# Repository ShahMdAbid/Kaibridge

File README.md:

<div align="center">
  <h1>Kaibridge</h1>
  <p><b>An open-source framework connecting AI agents to KiCad — enabling headless PCB design: architecting circuits from intent, sourcing verified components, compiling multi-sheet schematics, optimizing placement along with deterministic visual push-shove and routing alongside a human engineer in the loop</p>

</div>

<br/>

### Documentation

* [Core Capabilities](docs/core-capabilities.md)
* [System Architecture ](docs/architecture.md)
* [Contributing Guidelines](docs/contributing.md)
* [Changelog](CHANGELOG.md)
* [Issue Tracker](https://github.com/ShahMdAbid/Kaibridge/issues)

## Prerequisites & Installation

### 1. System Requirements
- **Python**: 3.10 or higher
- **KiCad**: KiCad 10.0 (or 9.0/8.0) with `kicad-cli` and bundled Python interpreter
- **Java**: Java 17+ LTS (required for Freerouting headless autorouting)

### 2. Installation
Clone the repository and install Kaibridge in editable mode:
```bash
git clone https://github.com/ShahMdAbid/Kaibridge.git
cd Kaibridge
pip install -e .
```

### 3. Autorouter Setup (Freerouting)
For headless trace routing (`kaibridge route`):
1. Download `freerouting-2.4.1.jar` from [Freerouting Releases](https://github.com/freerouting/freerouting/releases).
2. Place `freerouting-2.4.1.jar` in the Kaibridge root directory, or specify its location in `kicad_paths.json`.

### 4. Verify Installation & Test Suite
```bash
kaibridge --help
pytest
```

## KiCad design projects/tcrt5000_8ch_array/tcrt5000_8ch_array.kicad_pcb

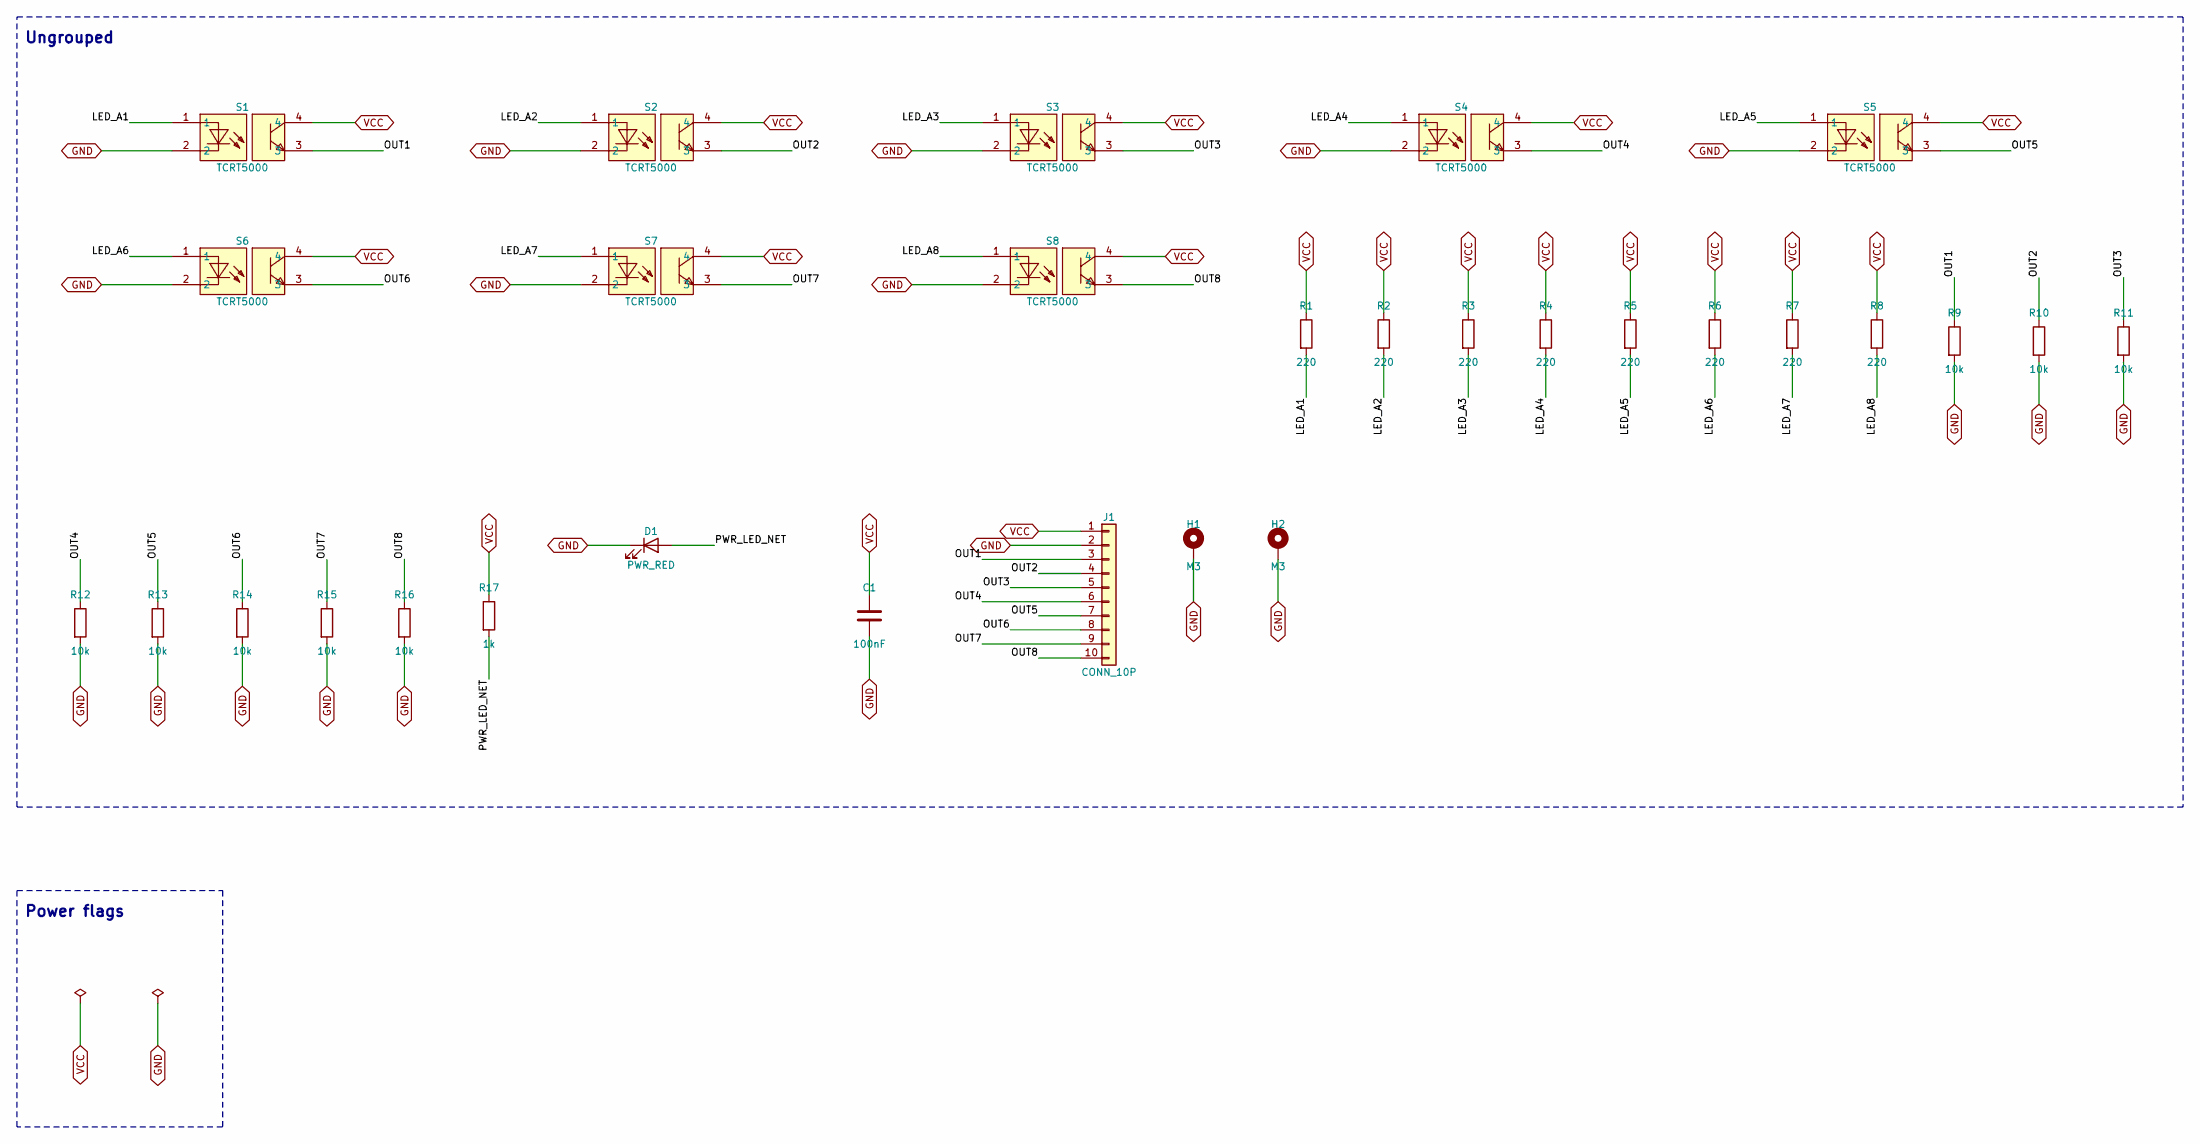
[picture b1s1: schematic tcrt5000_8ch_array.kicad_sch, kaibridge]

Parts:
C1: 100nF; C_Disc_D5.0mm_W2.5mm_P5.00mm; LCSC C66567
D1: PWR_RED; LED_D3.0mm; LCSC C1004
H1, H2: M3; MountingHole_3.2mm_M3_Pad
J1: CONN_10P; PinHeader_1x10_P2.54mm_Vertical; LCSC C2887
R1, R2, R3, R4, R5, R6, R7, R8: 220; R_Axial_DIN0207_L6.3mm_D2.5mm_P7.62mm_Horizontal; LCSC C65241
R9, R10, R11, R12, R13, R14, R15, R16: 10k; R_Axial_DIN0207_L6.3mm_D2.5mm_P7.62mm_Horizontal; LCSC C65240
R17: 1k; R_Axial_DIN0207_L6.3mm_D2.5mm_P7.62mm_Horizontal; LCSC C65242
S1, S2, S3, S4, S5, S6, S7, S8: TCRT5000; OPTO-TH_TCRT5000; LCSC C2984661

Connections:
GND: C1.2, D1.1 (K), H1.1, H2.1, J1.2, R9.2, R10.2, R11.2, R12.2, R13.2, R14.2, R15.2, R16.2, S1.2, S2.2, S3.2, S4.2, S5.2, S6.2, S7.2, S8.2
LED_A1: R1.2, S1.1
LED_A2: R2.2, S2.1
LED_A3: R3.2, S3.1
LED_A4: R4.2, S4.1
LED_A5: R5.2, S5.1
LED_A6: R6.2, S6.1
LED_A7: R7.2, S7.1
LED_A8: R8.2, S8.1
OUT1: J1.3, R9.1, S1.3
OUT2: J1.4, R10.1, S2.3
OUT3: J1.5, R11.1, S3.3
OUT4: J1.6, R12.1, S4.3
OUT5: J1.7, R13.1, S5.3
OUT6: J1.8, R14.1, S6.3
OUT7: J1.9, R15.1, S7.3
OUT8: J1.10, R16.1, S8.3
PWR_LED_NET: D1.2 (A), R17.2
VCC: C1.1, J1.1, R1.1, R2.1, R3.1, R4.1, R5.1, R6.1, R7.1, R8.1, R17.1, S1.4, S2.4, S3.4, S4.4, S5.4, S6.4, S7.4, S8.4

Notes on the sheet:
Ungrouped
Power flags

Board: 2 copper layers, 30 parts (0 on the bottom side), 19 nets, no tracks yet.

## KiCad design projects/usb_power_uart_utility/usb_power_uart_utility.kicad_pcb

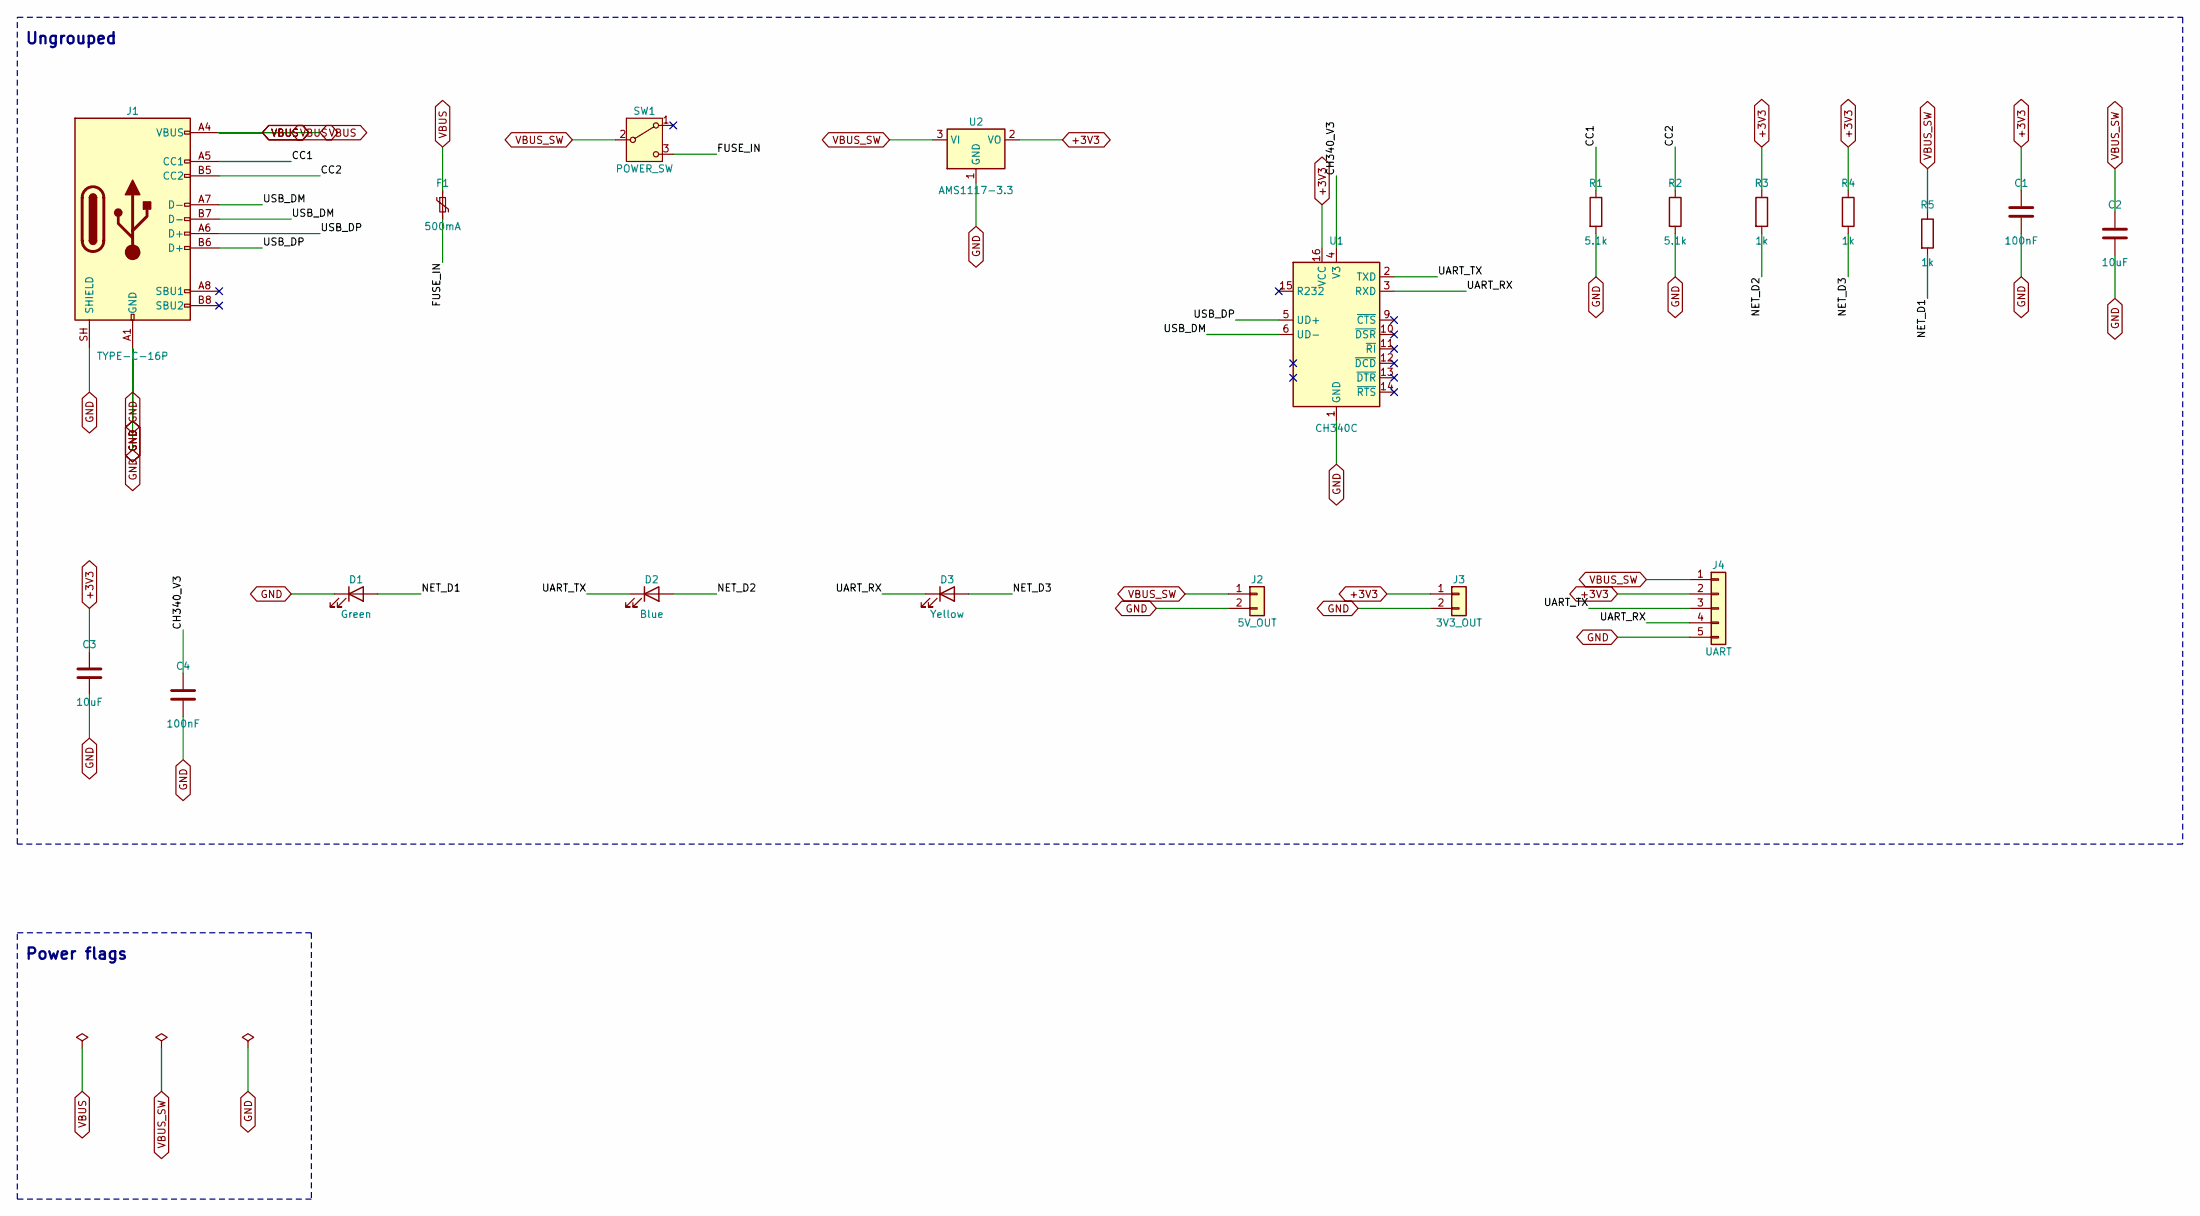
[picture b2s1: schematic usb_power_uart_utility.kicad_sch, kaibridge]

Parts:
C1, C4: 100nF; C_0805_2012Metric; JLCPCB_Class Basic Part
C2, C3: 10uF; C_0805_2012Metric; JLCPCB_Class Basic Part
D1: Green; LED_0805_2012Metric; JLCPCB_Class Basic Part
D2: Blue; LED_0805_2012Metric; JLCPCB_Class Basic Part
D3: Yellow; LED_0805_2012Metric; JLCPCB_Class Basic Part
F1: 500mA; Fuse_1206_3216Metric; JLCPCB_Class Basic Part
J1: TYPE-C-16P; USB_C_Receptacle_HRO_TYPE-C-31-M-12; JLCPCB_Class Basic Part
J2: 5V_OUT; PinHeader_1x02_P2.54mm_Vertical
J3: 3V3_OUT; PinHeader_1x02_P2.54mm_Vertical
J4: UART; PinHeader_1x05_P2.54mm_Vertical
R1, R2: 5.1k; R_0805_2012Metric; JLCPCB_Class Basic Part
R3, R4, R5: 1k; R_0805_2012Metric; JLCPCB_Class Basic Part
SW1: POWER_SW; SW_SPDT_PCM12; JLCPCB_Class Basic Part
U1: CH340C; SOIC-16_3.9x9.9mm_P1.27mm; JLCPCB_Class Basic Part
U2: AMS1117-3.3; SOT-223-3_TabPin2; JLCPCB_Class Basic Part

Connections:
+3V3: C1.1, C3.1, J3.1, J4.2, R3.1, R4.1, U1.16 (VCC), U2.2 (VO)
CC1: J1.A5 (CC1), R1.1
CC2: J1.B5 (CC2), R2.1
CH340_V3: C4.1, U1.4 (V3)
FUSE_IN: F1.2, SW1.3 (C)
GND: C1.2, C2.2, C3.2, C4.2, D1.1 (K), J1.A1 (GND), J1.A12 (GND), J1.B1 (GND), J1.B12 (GND), J1.SH (SHIELD), J2.2, J3.2, J4.5, R1.2, R2.2, U1.1 (GND), U2.1 (GND)
NET_D1: D1.2 (A), R5.2
NET_D2: D2.2 (A), R3.2
NET_D3: D3.2 (A), R4.2
UART_RX: D3.1 (K), J4.4, U1.3 (RXD)
UART_TX: D2.1 (K), J4.3, U1.2 (TXD)
USB_DM: J1.A7 (D-), J1.B7 (D-), U1.6 (UD-)
USB_DP: J1.A6 (D+), J1.B6 (D+), U1.5 (UD+)
VBUS: F1.1, J1.A4 (VBUS), J1.A9 (VBUS), J1.B4 (VBUS), J1.B9 (VBUS)
VBUS_SW: C2.1, J2.1, J4.1, R5.1, SW1.2 (B), U2.3 (VI)

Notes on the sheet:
Ungrouped
Power flags

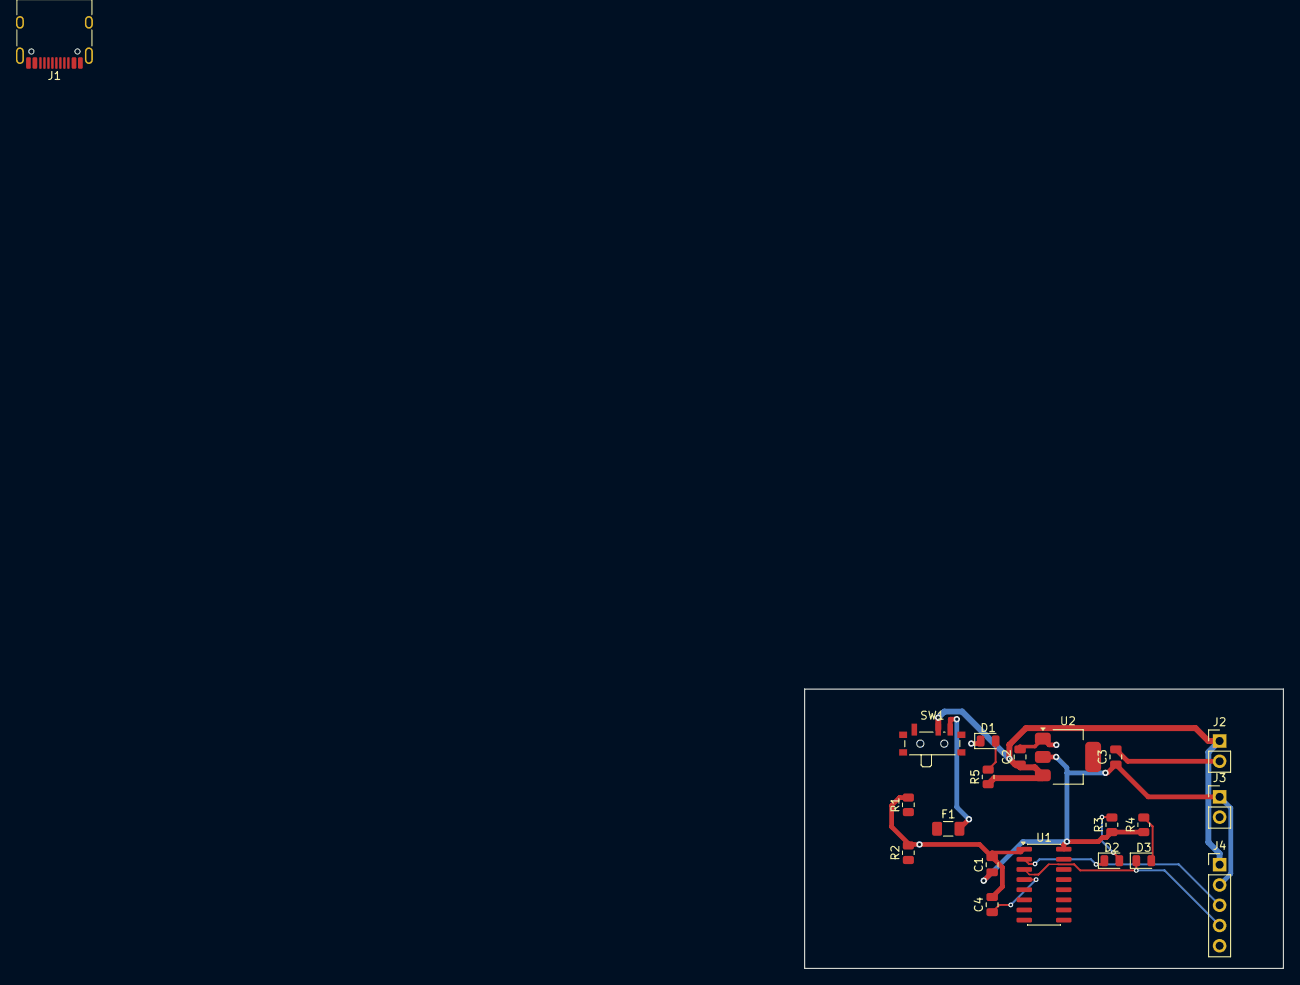
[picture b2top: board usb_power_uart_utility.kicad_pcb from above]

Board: 2 copper layers, 60.0 x 35.0 mm, 20 parts (0 on the bottom side), 15 nets.

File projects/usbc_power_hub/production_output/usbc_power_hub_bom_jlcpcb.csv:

Comment,Designator,Footprint,LCSC Part #
1.2k,R3,R_0805_2012Metric,
10uF,"C1,C2,C3",C_0805_2012Metric,
1k,"R4,R5,R6",R_0805_2012Metric,
5.1k,"R1,R2",R_0805_2012Metric,
AMS1117-3.3,U2,SOT-223-3_L6.5-W3.4-P2.30-LS7.0-BR,
CHRG_RED,D1,LED_0805_2012Metric,
LiPo_BAT,J2,PinHeader_1x02_P2.54mm_Vertical,
PWR_3V3_BLU,D3,LED_0805_2012Metric,
Power_Out,J3,PinHeader_1x04_P2.54mm_Vertical,
STDBY_GRN,D2,LED_0805_2012Metric,
TP4056,U1,ESOP-8_L4.9-W3.9-P1.27-LS6.0-BL-EP,
USB_C_16P,J1,USB_C_Receptacle_HRO_TYPE-C-31-M-12,

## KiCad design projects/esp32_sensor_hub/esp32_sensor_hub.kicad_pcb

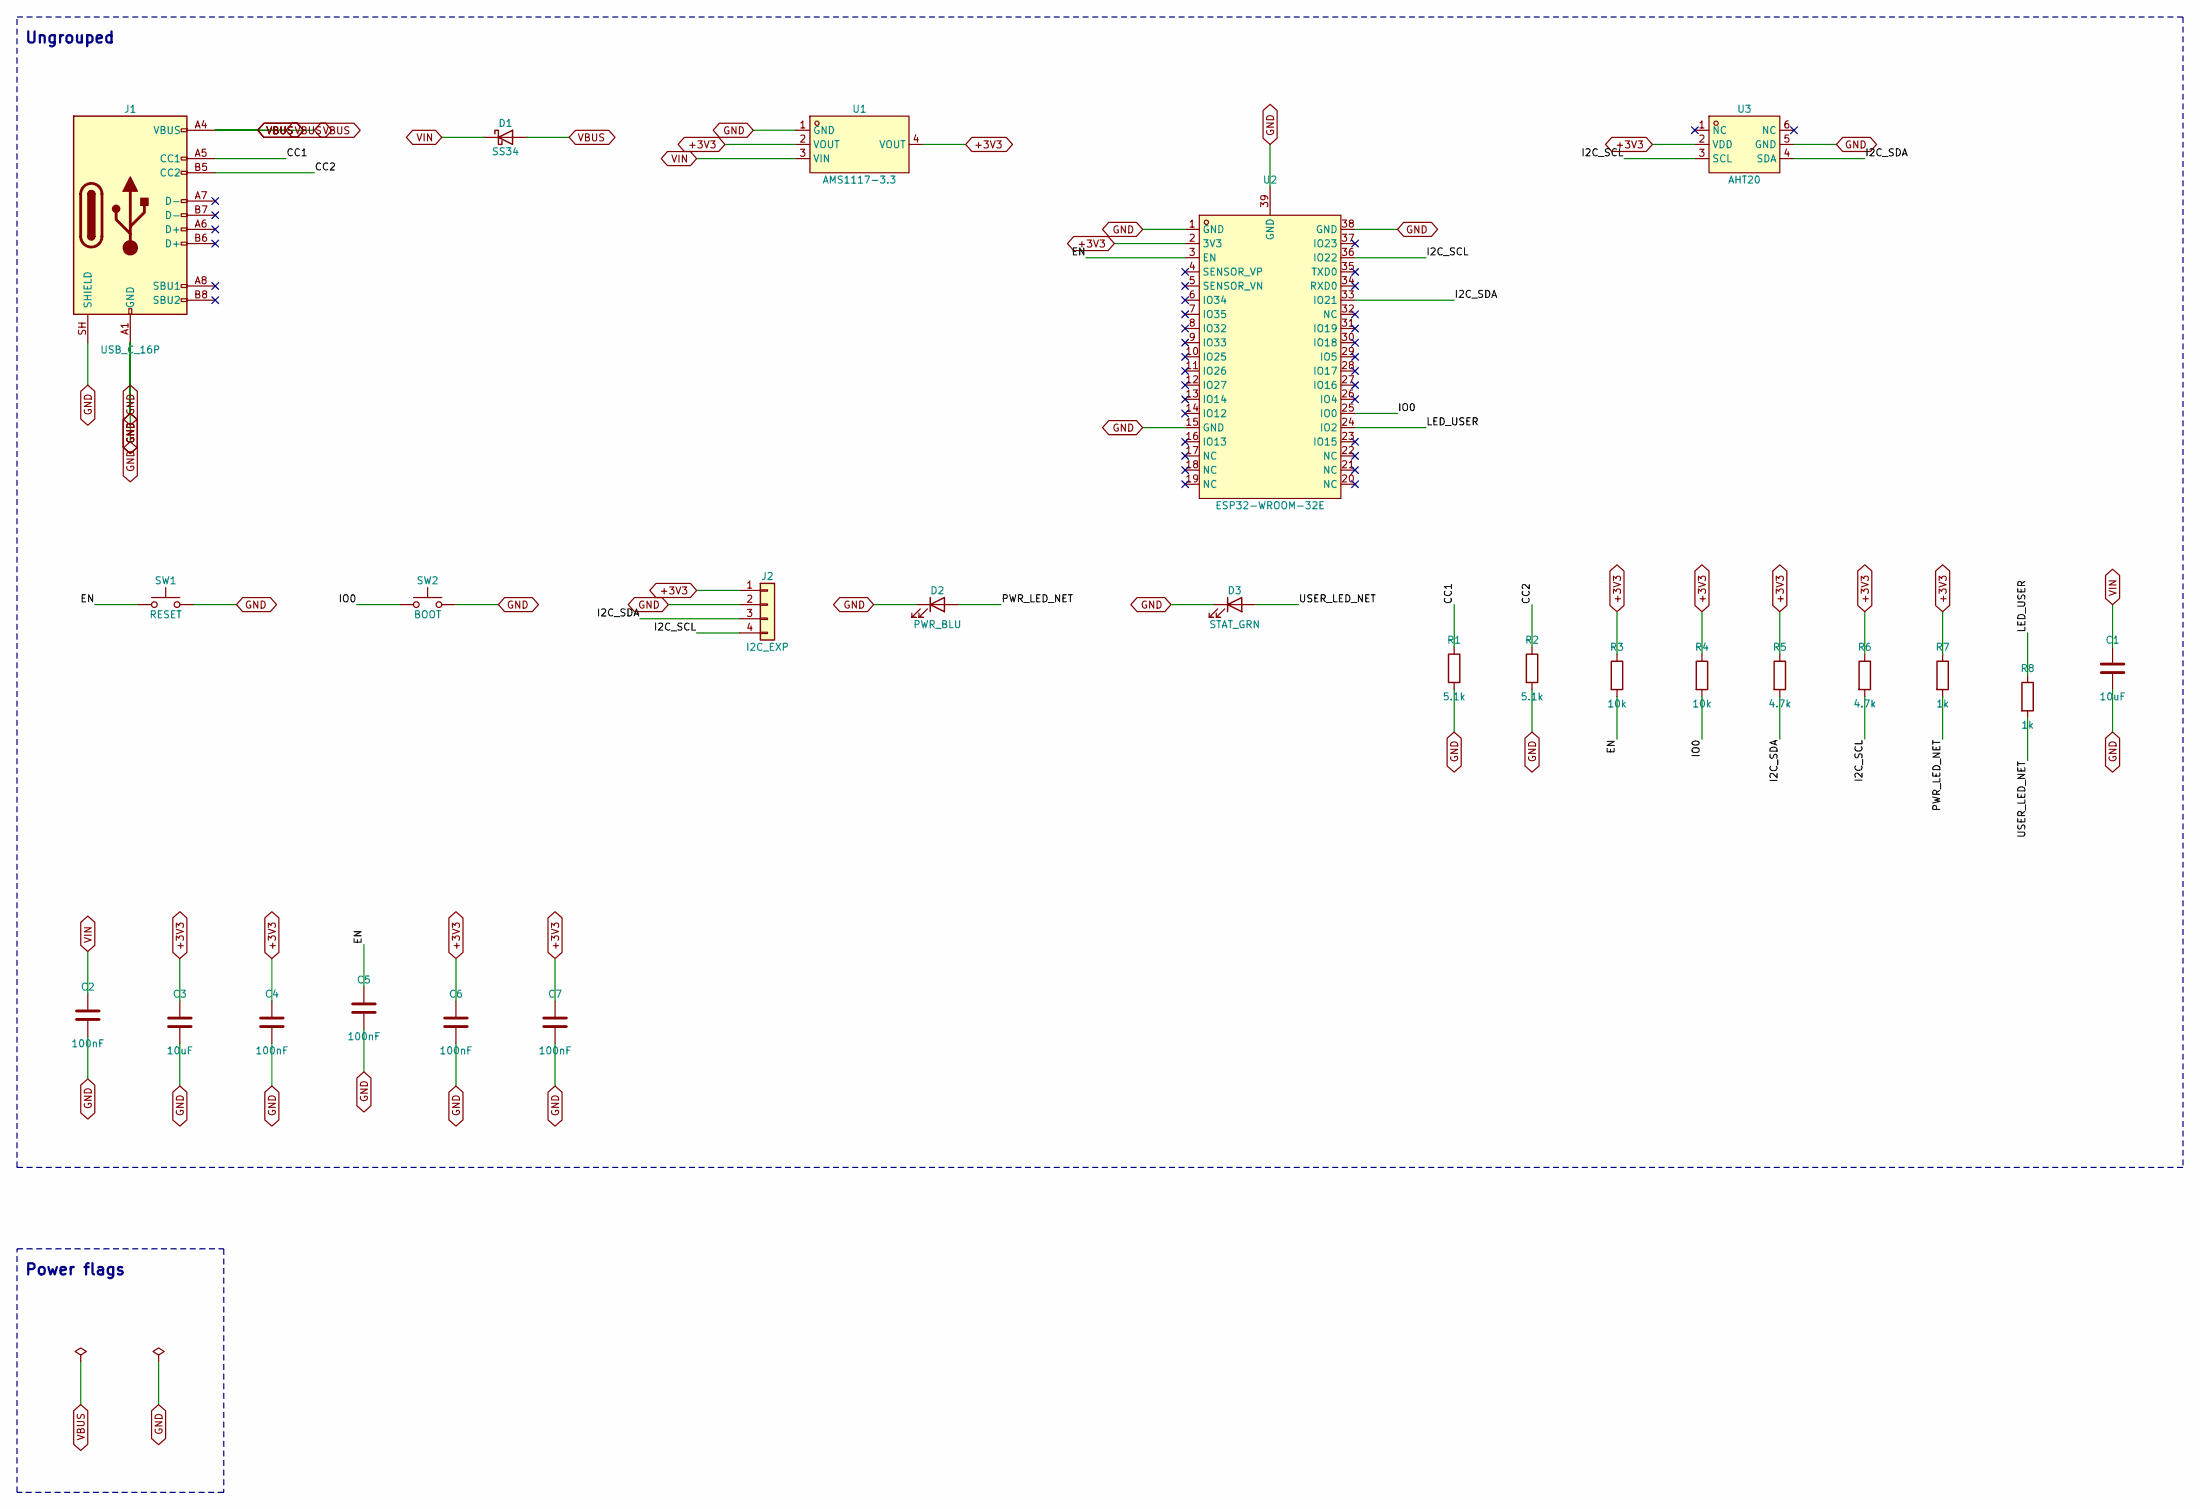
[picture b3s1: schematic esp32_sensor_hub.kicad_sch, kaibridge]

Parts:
C1, C3: 10uF; C_0805_2012Metric; LCSC C15850
C2, C4, C5, C6, C7: 100nF; C_0805_2012Metric; LCSC C28233
D1: SS34; D_SMA; LCSC C8678
D2: PWR_BLU; LED_0805_2012Metric; LCSC C84258
D3: STAT_GRN; LED_0805_2012Metric; LCSC C84257
J1: USB_C_16P; USB_C_Receptacle_HRO_TYPE-C-31-M-12; LCSC C165948
J2: I2C_EXP; PinHeader_1x04_P2.54mm_Vertical; LCSC C2883
R1, R2: 5.1k; R_0805_2012Metric; LCSC C23186
R3, R4: 10k; R_0805_2012Metric; LCSC C17414
R5, R6: 4.7k; R_0805_2012Metric; LCSC C23162
R7, R8: 1k; R_0805_2012Metric; LCSC C17513
SW1: RESET; SW_SPST_PTS645Sx43SMTR92; LCSC C318884
SW2: BOOT; SW_SPST_PTS645Sx43SMTR92; LCSC C318884
U1: AMS1117-3.3; SOT-223-3_L6.5-W3.4-P2.30-LS7.0-BR; LCSC C6186
U2: ESP32-WROOM-32E; WIFI-SMD_ESP32-WROOM-32E; LCSC C701341
U3: AHT20; SENSOR-SMD-6_AHT20; LCSC C3012622

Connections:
+3V3: C3.1, C4.1, C6.1, C7.1, J2.1, R3.1, R4.1, R5.1, R6.1, R7.1, U1.2 (VOUT), U1.4 (VOUT), U2.2 (3V3), U3.2 (VDD)
CC1: J1.A5 (CC1), R1.1
CC2: J1.B5 (CC2), R2.1
EN: C5.1, R3.2, SW1.1, U2.3 (EN)
GND: C1.2, C2.2, C3.2, C4.2, C5.2, C6.2, C7.2, D2.1 (K), D3.1 (K), J1.A1 (GND), J1.A12 (GND), J1.B1 (GND), J1.B12 (GND), J1.SH (SHIELD), J2.2, R1.2, R2.2, SW1.2, SW2.2, U1.1 (GND), U2.1 (GND), U2.15 (GND), U2.38 (GND), U2.39 (GND), U3.5 (GND)
I2C_SCL: J2.4, R6.2, U2.36 (IO22), U3.3 (SCL)
I2C_SDA: J2.3, R5.2, U2.33 (IO21), U3.4 (SDA)
IO0: R4.2, SW2.1, U2.25 (IO0)
LED_USER: R8.1, U2.24 (IO2)
PWR_LED_NET: D2.2 (A), R7.2
USER_LED_NET: D3.2 (A), R8.2
VBUS: D1.2 (A), J1.A4 (VBUS), J1.A9 (VBUS), J1.B4 (VBUS), J1.B9 (VBUS)
VIN: C1.1, C2.1, D1.1 (K), U1.3 (VIN)

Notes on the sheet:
Ungrouped
Power flags

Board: 2 copper layers, 25 parts (0 on the bottom side), 13 nets, no tracks yet.

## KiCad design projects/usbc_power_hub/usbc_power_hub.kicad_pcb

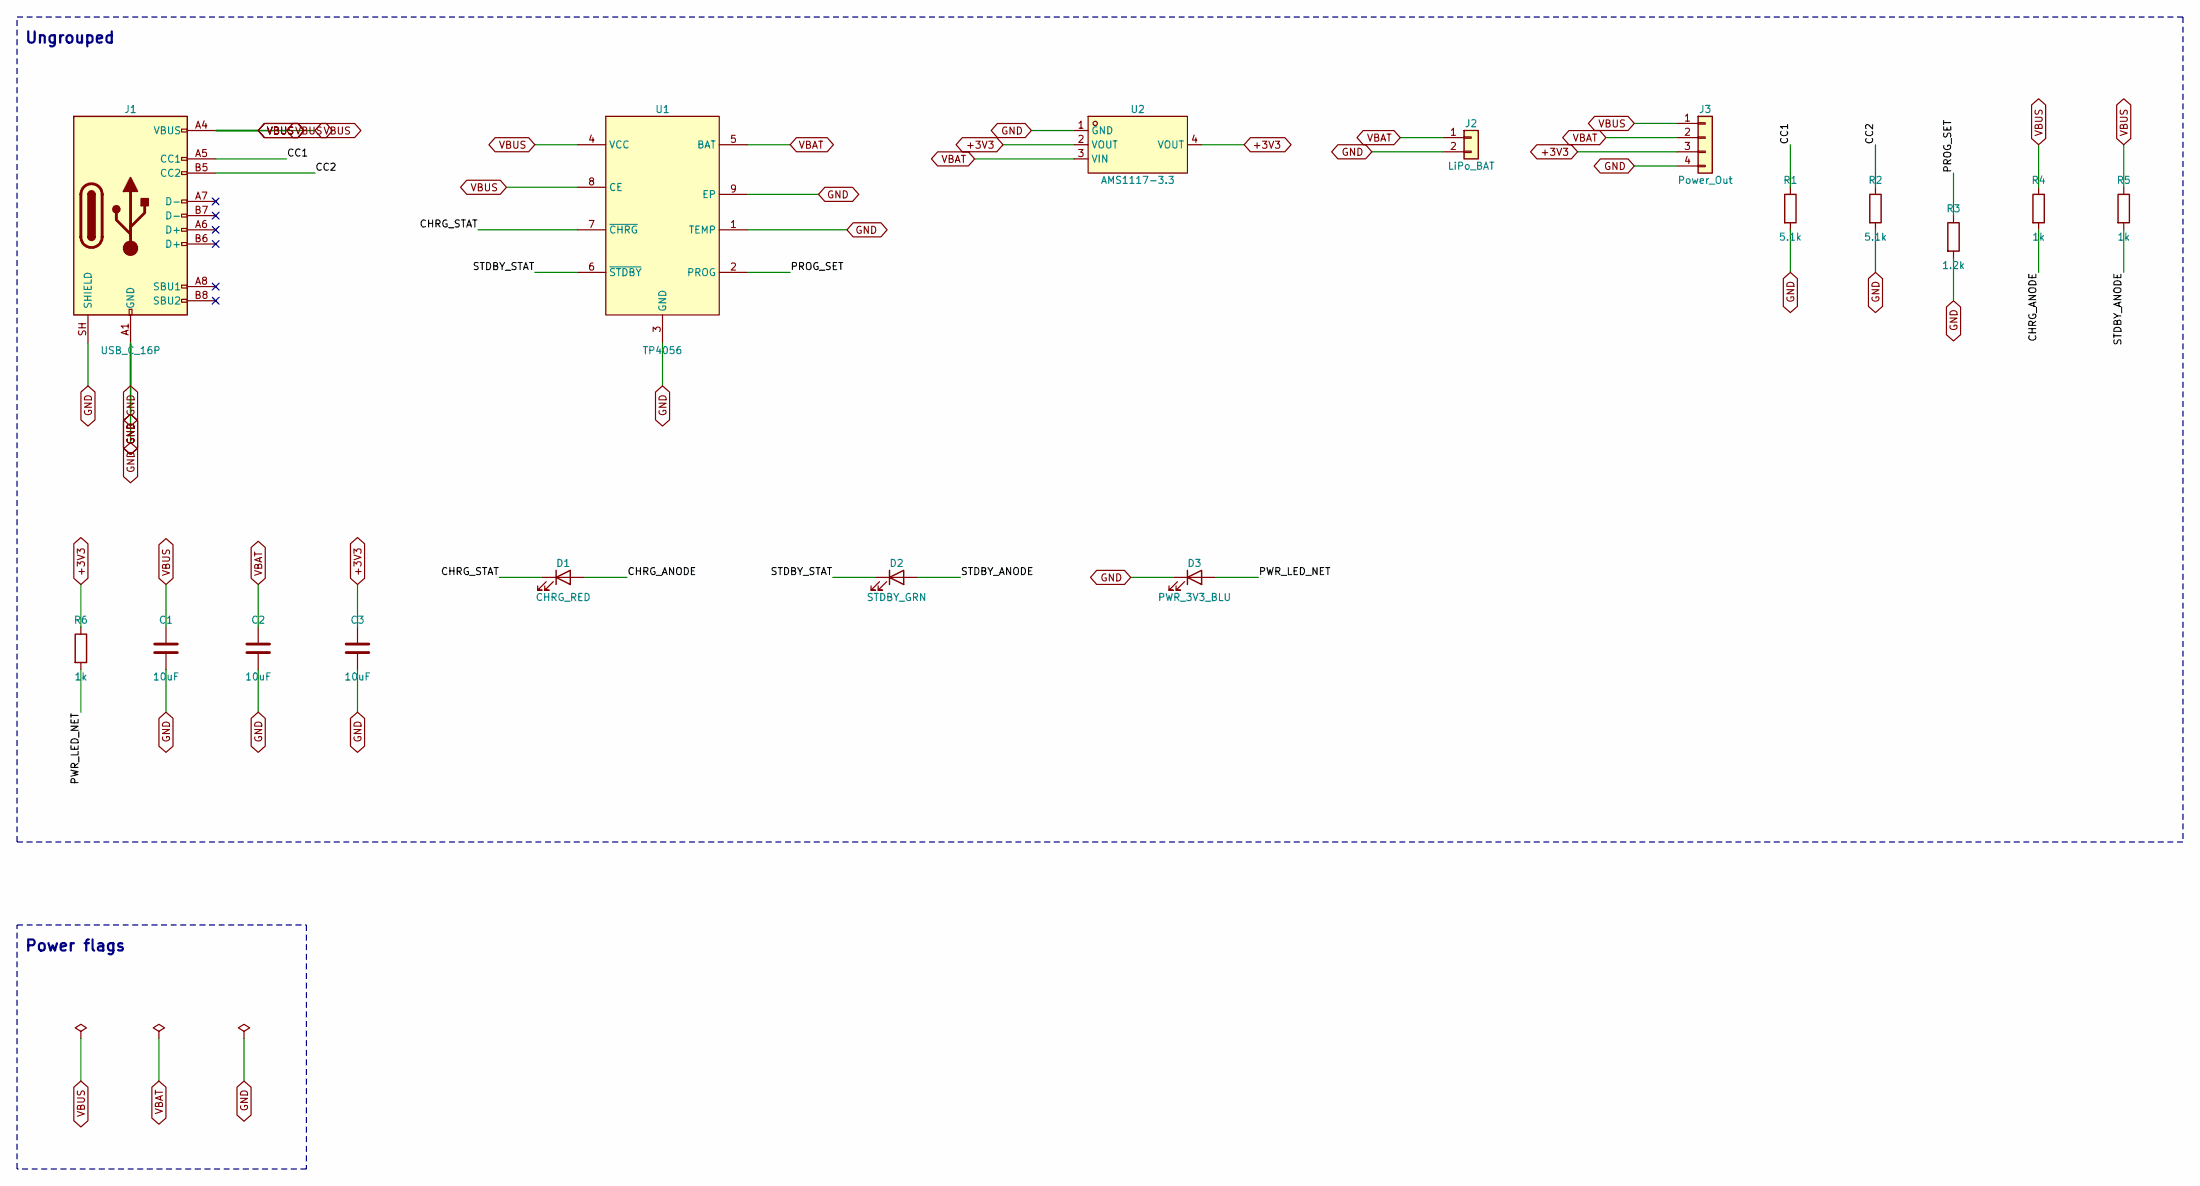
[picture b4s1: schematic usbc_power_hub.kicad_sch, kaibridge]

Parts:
C1, C2, C3: 10uF; C_0805_2012Metric; LCSC C15850
D1: CHRG_RED; LED_0805_2012Metric; LCSC C84256
D2: STDBY_GRN; LED_0805_2012Metric; LCSC C84257
D3: PWR_3V3_BLU; LED_0805_2012Metric; LCSC C84258
J1: USB_C_16P; USB_C_Receptacle_HRO_TYPE-C-31-M-12; LCSC C165948
J2: LiPo_BAT; PinHeader_1x02_P2.54mm_Vertical; LCSC C2943261
J3: Power_Out; PinHeader_1x04_P2.54mm_Vertical; LCSC C2883
R1, R2: 5.1k; R_0805_2012Metric; LCSC C23186
R3: 1.2k; R_0805_2012Metric; LCSC C22986
R4, R5, R6: 1k; R_0805_2012Metric; LCSC C17513
U1: TP4056; ESOP-8_L4.9-W3.9-P1.27-LS6.0-BL-EP; LCSC C16581
U2: AMS1117-3.3; SOT-223-3_L6.5-W3.4-P2.30-LS7.0-BR; LCSC C6186

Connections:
+3V3: C3.1, J3.3, R6.1, U2.2 (VOUT), U2.4 (VOUT)
CC1: J1.A5 (CC1), R1.1
CC2: J1.B5 (CC2), R2.1
CHRG_ANODE: D1.2 (A), R4.2
CHRG_STAT: D1.1 (K), U1.7 (~CHRG)
GND: C1.2, C2.2, C3.2, D3.1 (K), J1.A1 (GND), J1.A12 (GND), J1.B1 (GND), J1.B12 (GND), J1.SH (SHIELD), J2.2, J3.4, R1.2, R2.2, R3.2, U1.1 (TEMP), U1.3 (GND), U1.9 (EP), U2.1 (GND)
PROG_SET: R3.1, U1.2 (PROG)
PWR_LED_NET: D3.2 (A), R6.2
STDBY_ANODE: D2.2 (A), R5.2
STDBY_STAT: D2.1 (K), U1.6 (~STDBY)
VBAT: C2.1, J2.1, J3.2, U1.5 (BAT), U2.3 (VIN)
VBUS: C1.1, J1.A4 (VBUS), J1.A9 (VBUS), J1.B4 (VBUS), J1.B9 (VBUS), J3.1, R4.1, R5.1, U1.4 (VCC), U1.8 (CE)

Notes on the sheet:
Ungrouped
Power flags

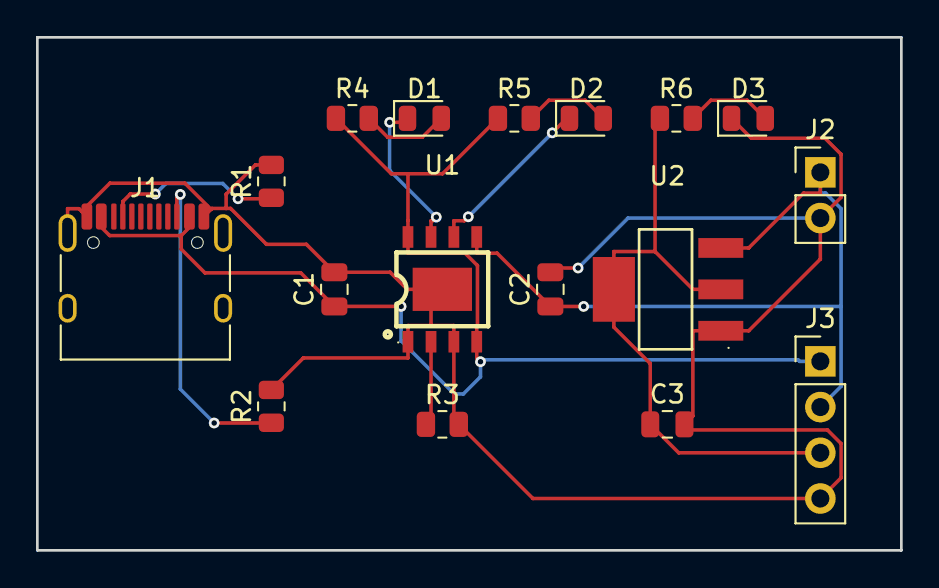
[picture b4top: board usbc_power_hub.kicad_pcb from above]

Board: 2 copper layers, 48.0 x 28.5 mm, 17 parts (0 on the bottom side), 12 nets.

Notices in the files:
README.md:
License: AGPL v3.0
